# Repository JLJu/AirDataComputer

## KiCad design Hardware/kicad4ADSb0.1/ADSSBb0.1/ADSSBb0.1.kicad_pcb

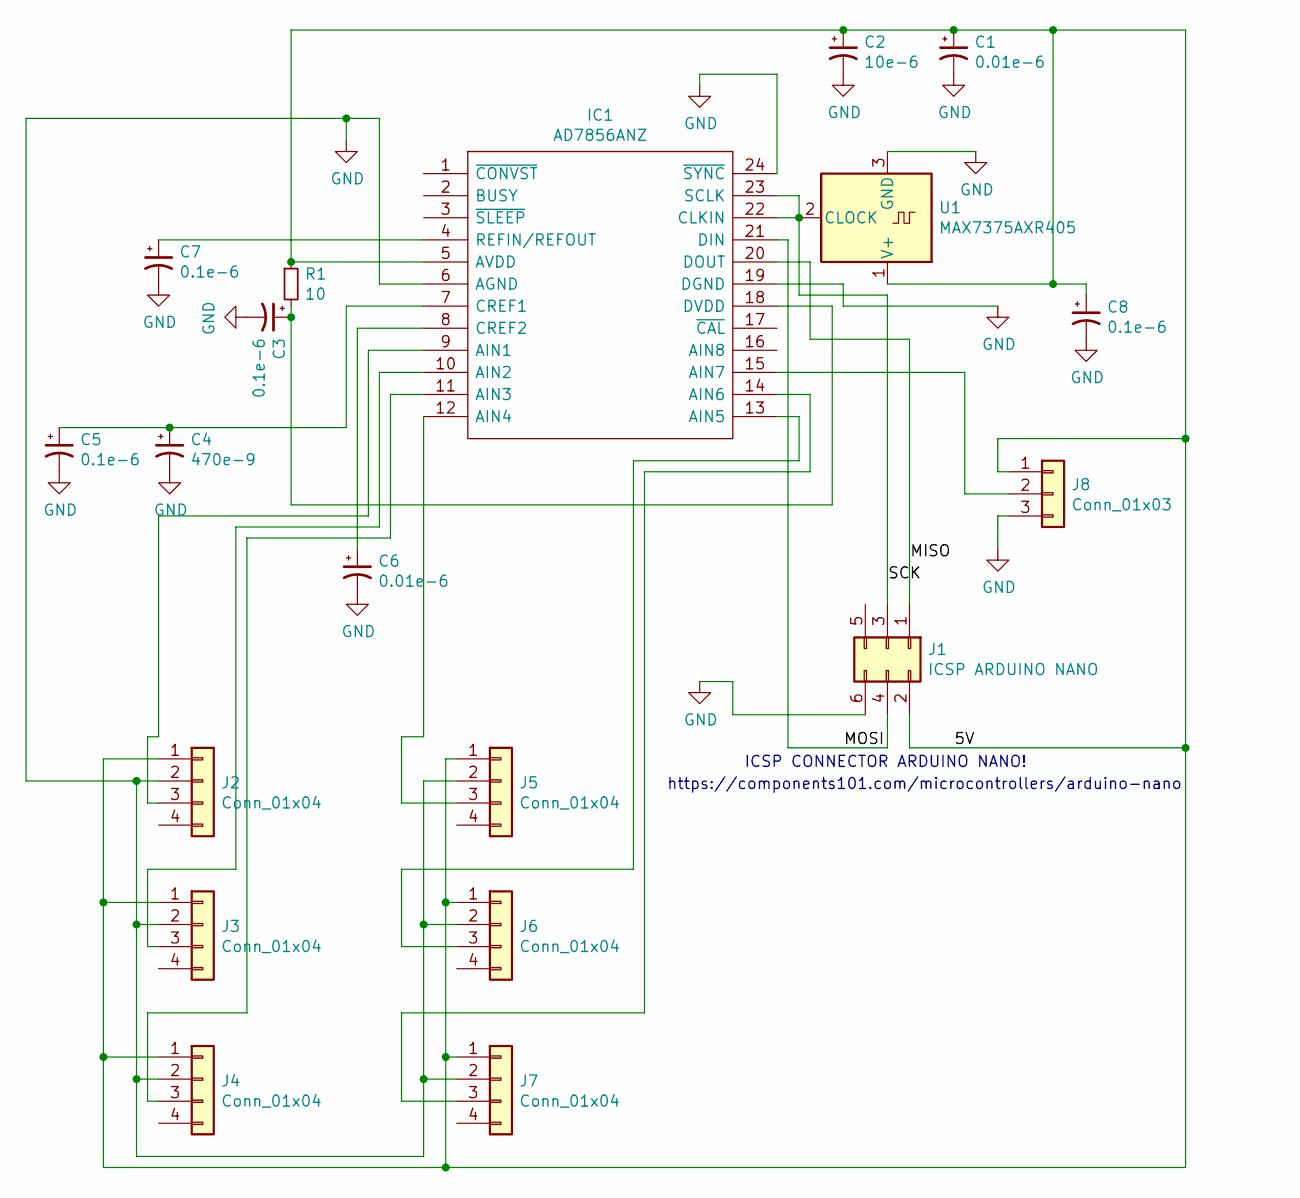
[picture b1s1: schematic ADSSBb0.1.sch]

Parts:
C1, C6: 0.01e-6; CP_EIA-2012-12_Kemet-R_Pad1.30x1.05mm_HandSolder
C2: 10e-6; CP_EIA-2012-12_Kemet-R_Pad1.30x1.05mm_HandSolder
C3, C5, C7, C8: 0.1e-6; CP_EIA-2012-12_Kemet-R_Pad1.30x1.05mm_HandSolder
C4: 470e-9; CP_EIA-2012-12_Kemet-R_Pad1.30x1.05mm_HandSolder
IC1: AD7856ANZ; SOIC-24W_7.5x15.4mm_P1.27mm; Mouser Part Number 584-AD7856ANZ
J1: ICSP ARDUINO NANO; PinSocket_2x03_P2.54mm_Vertical
J2, J3, J4, J5, J6, J7: Conn_01x04; PinSocket_1x04_P2.54mm_Vertical
J8: Conn_01x03; PinHeader_1x03_P2.54mm_Vertical
R1: 10; R_1206_3216Metric
U1: MAX7375AXR405; SOT-323_SC-70

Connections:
/5V: C1.1, C2.1, C8.1, IC1.5 (AVDD), J1.2, J2.1, J3.1, J4.1, J5.1, J6.1, J7.1, J8.1, R1.1, U1.1 (V+)
/MISO: IC1.20 (DOUT), J1.1
/MOSI: IC1.21 (DIN), J1.4
/SCK: IC1.22 (CLKIN), IC1.23 (SCLK), J1.3, U1.2 (CLOCK)
GND: C1.2, C2.2, C3.2, C4.2, C5.2, C6.2, C7.2, C8.2, IC1.6 (AGND), IC1.19 (DGND), IC1.24 (~SYNC), J1.6, J2.2, J3.2, J4.2, J5.2, J6.2, J7.2, J8.3, U1.3 (GND)
unnamed: C3.1, IC1.18 (DVDD), R1.2
unnamed: C4.1, C5.1, IC1.7 (CREF1)
unnamed: C6.1, IC1.8 (CREF2)
unnamed: C7.1, IC1.4 (REFIN/REFOUT)
unnamed: IC1.9 (AIN1), J2.3
unnamed: IC1.10 (AIN2), J3.3
unnamed: IC1.11 (AIN3), J4.3
unnamed: IC1.12 (AIN4), J5.3
unnamed: IC1.13 (AIN5), J6.3
unnamed: IC1.14 (AIN6), J7.3
unnamed: IC1.15 (AIN7), J8.2

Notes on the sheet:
https://components101.com/microcontrollers/arduino-nano
ICSP CONNECTOR ARDUINO NANO!

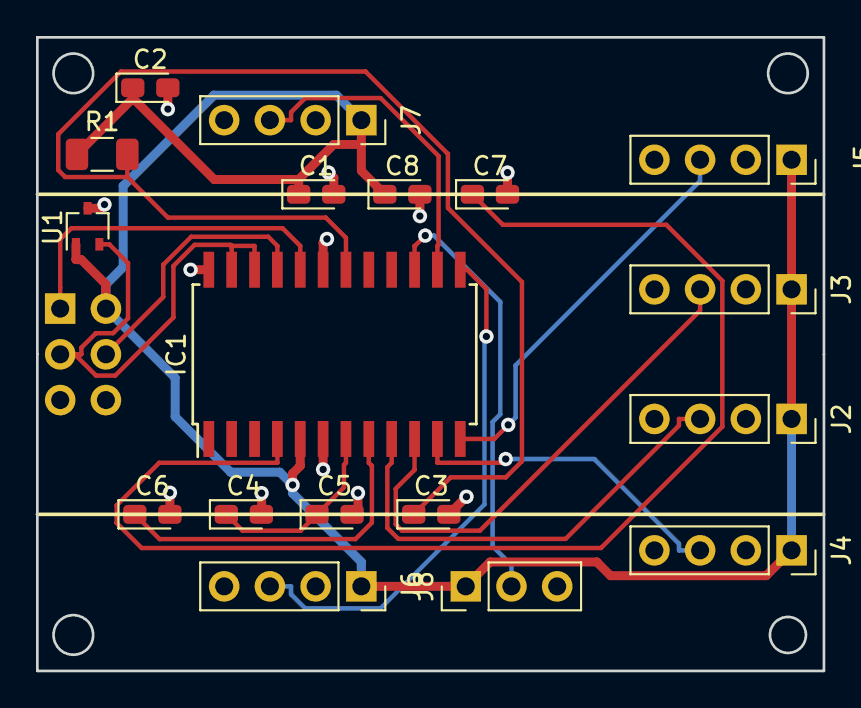
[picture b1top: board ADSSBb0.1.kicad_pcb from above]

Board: 2 copper layers, 43.7 x 35.2 mm, 19 parts (1 on the bottom side), 16 nets.

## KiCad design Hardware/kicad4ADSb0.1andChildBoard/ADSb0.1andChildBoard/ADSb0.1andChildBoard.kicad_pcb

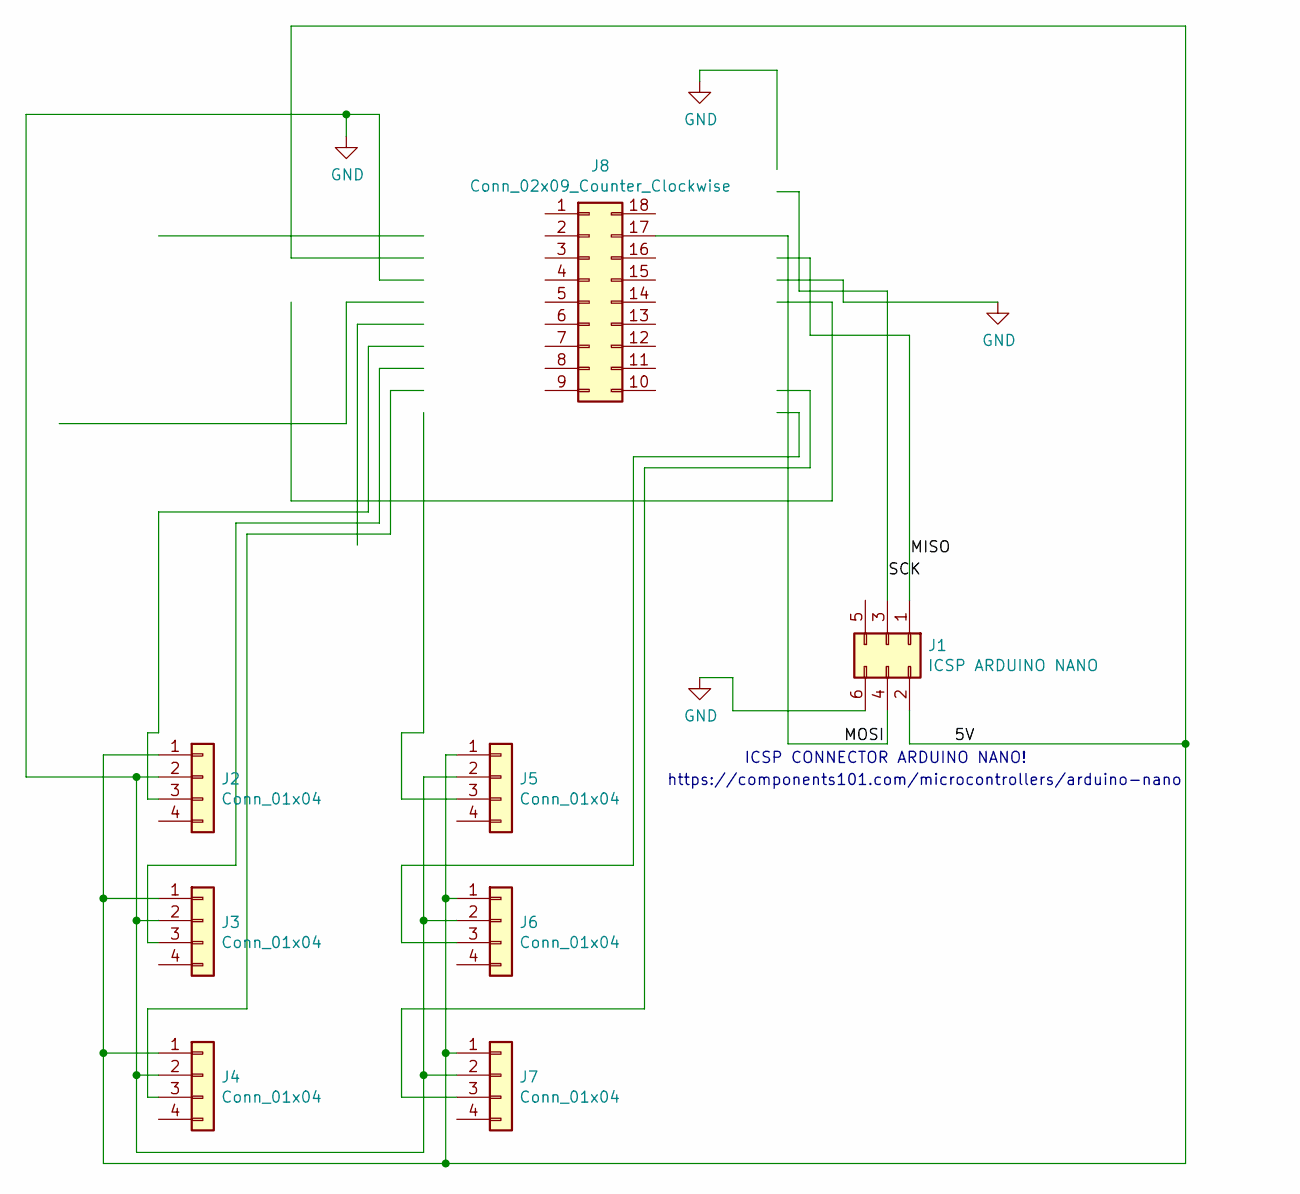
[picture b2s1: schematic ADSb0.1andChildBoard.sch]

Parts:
J1: ICSP ARDUINO NANO; PinSocket_2x03_P2.54mm_Vertical
J2, J3, J4, J5, J6, J7: Conn_01x04; PinSocket_1x04_P2.54mm_Vertical
J8: Conn_02x09_Counter_Clockwise; Molex_Picoflex_90325-0018_2x09_P1.27mm_Vertical

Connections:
/5V: J1.2, J2.1, J3.1, J4.1, J5.1, J6.1, J7.1
/MISO: J1.1
/MOSI: J1.4, J8.17
/SCK: J1.3
GND: J1.6, J2.2, J3.2, J4.2, J5.2, J6.2, J7.2

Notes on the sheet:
https://components101.com/microcontrollers/arduino-nano
ICSP CONNECTOR ARDUINO NANO!

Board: 2 copper layers, 8 parts (1 on the bottom side), 3 nets, no tracks yet.

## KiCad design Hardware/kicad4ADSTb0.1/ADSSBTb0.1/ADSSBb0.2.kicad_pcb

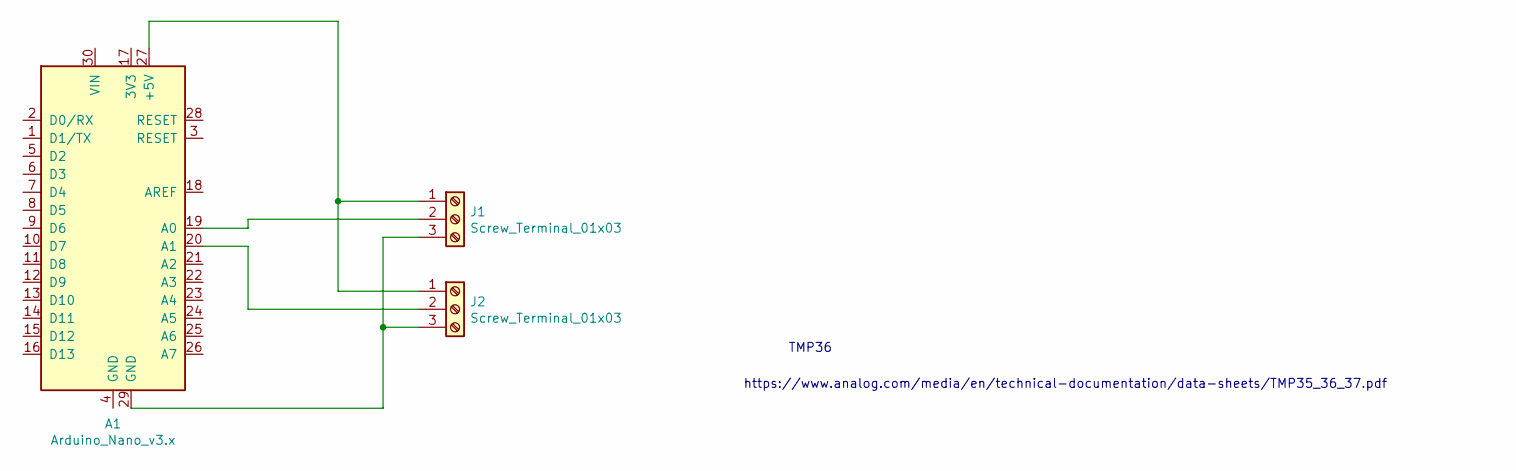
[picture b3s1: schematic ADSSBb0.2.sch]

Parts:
A1: Arduino_Nano_v3.x; Arduino_Nano
J1, J2: Screw_Terminal_01x03; TerminalBlock_4Ucon_1x03_P3.50mm_Vertical

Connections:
unnamed: A1.19 (A0), J1.2
unnamed: A1.20 (A1), J2.2
unnamed: A1.27 (+5V), J1.1, J2.1
unnamed: A1.29 (GND), J1.3, J2.3

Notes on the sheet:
https://www.analog.com/media/en/technical-documentation/data-sheets/TMP35_36_37.pdf
TMP36

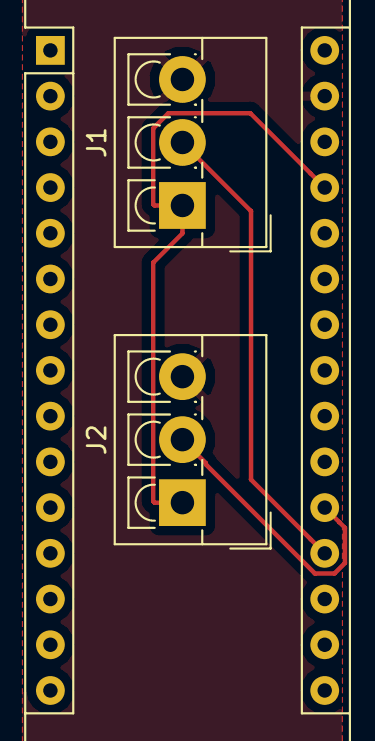
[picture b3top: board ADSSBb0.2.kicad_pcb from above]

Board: 2 copper layers, 3 parts (0 on the bottom side), 4 nets.

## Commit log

2019-01-24 Temperature sensor board
    Kicad
2019-01-24 Kicad
    up
2019-01-24 Kicad mockup
    Kicad mockup
2019-01-27 Kicad up
2019-01-27 Up Kicad
2019-01-27 kicad rup
2019-01-28 Ricad
    New PCB
2019-01-28 3 Holes PCB
2019-01-29 SIL moved
